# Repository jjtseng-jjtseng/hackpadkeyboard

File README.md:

# My HackPad Keyboard

A keyboard that can type an absurdly large amount of characters in a short space.
By combining the 16 keys with the knob, each turn of the knob makes each key type a different thing. This way, you can go from your normal A B C's to weird hieroglyphics.

# Features/Things used:

- 3d printed case (bottom section with a usb c hole wita top cover with a knob and key hole(s))
- 99.5 x99.5 mm pcb with a 4x4 matrix of buttons on it (+ knob)
- 16 LED's for each of buttons (cool lighting effects)

# CAD
Used fusion 360
Pretty easy. Bottom case with usb c hole + top case with key, knob, and LED holes.

# PCB

PCB pics attached below.
Kicad used

Schematic

PCB
CAD render:

# Firmware:
Python with a main.py used.

#How the final product should look:

Main.py

# BOM

Everything that is needed to make this:

- 1x custom pcb
- 1x Rotary encoder
- 1x Seeed XIAO RP2040
- 16x SK6812MINI-E RGB LEDs
- 16x DSA keycaps
- 16x 1N4148 Diodes

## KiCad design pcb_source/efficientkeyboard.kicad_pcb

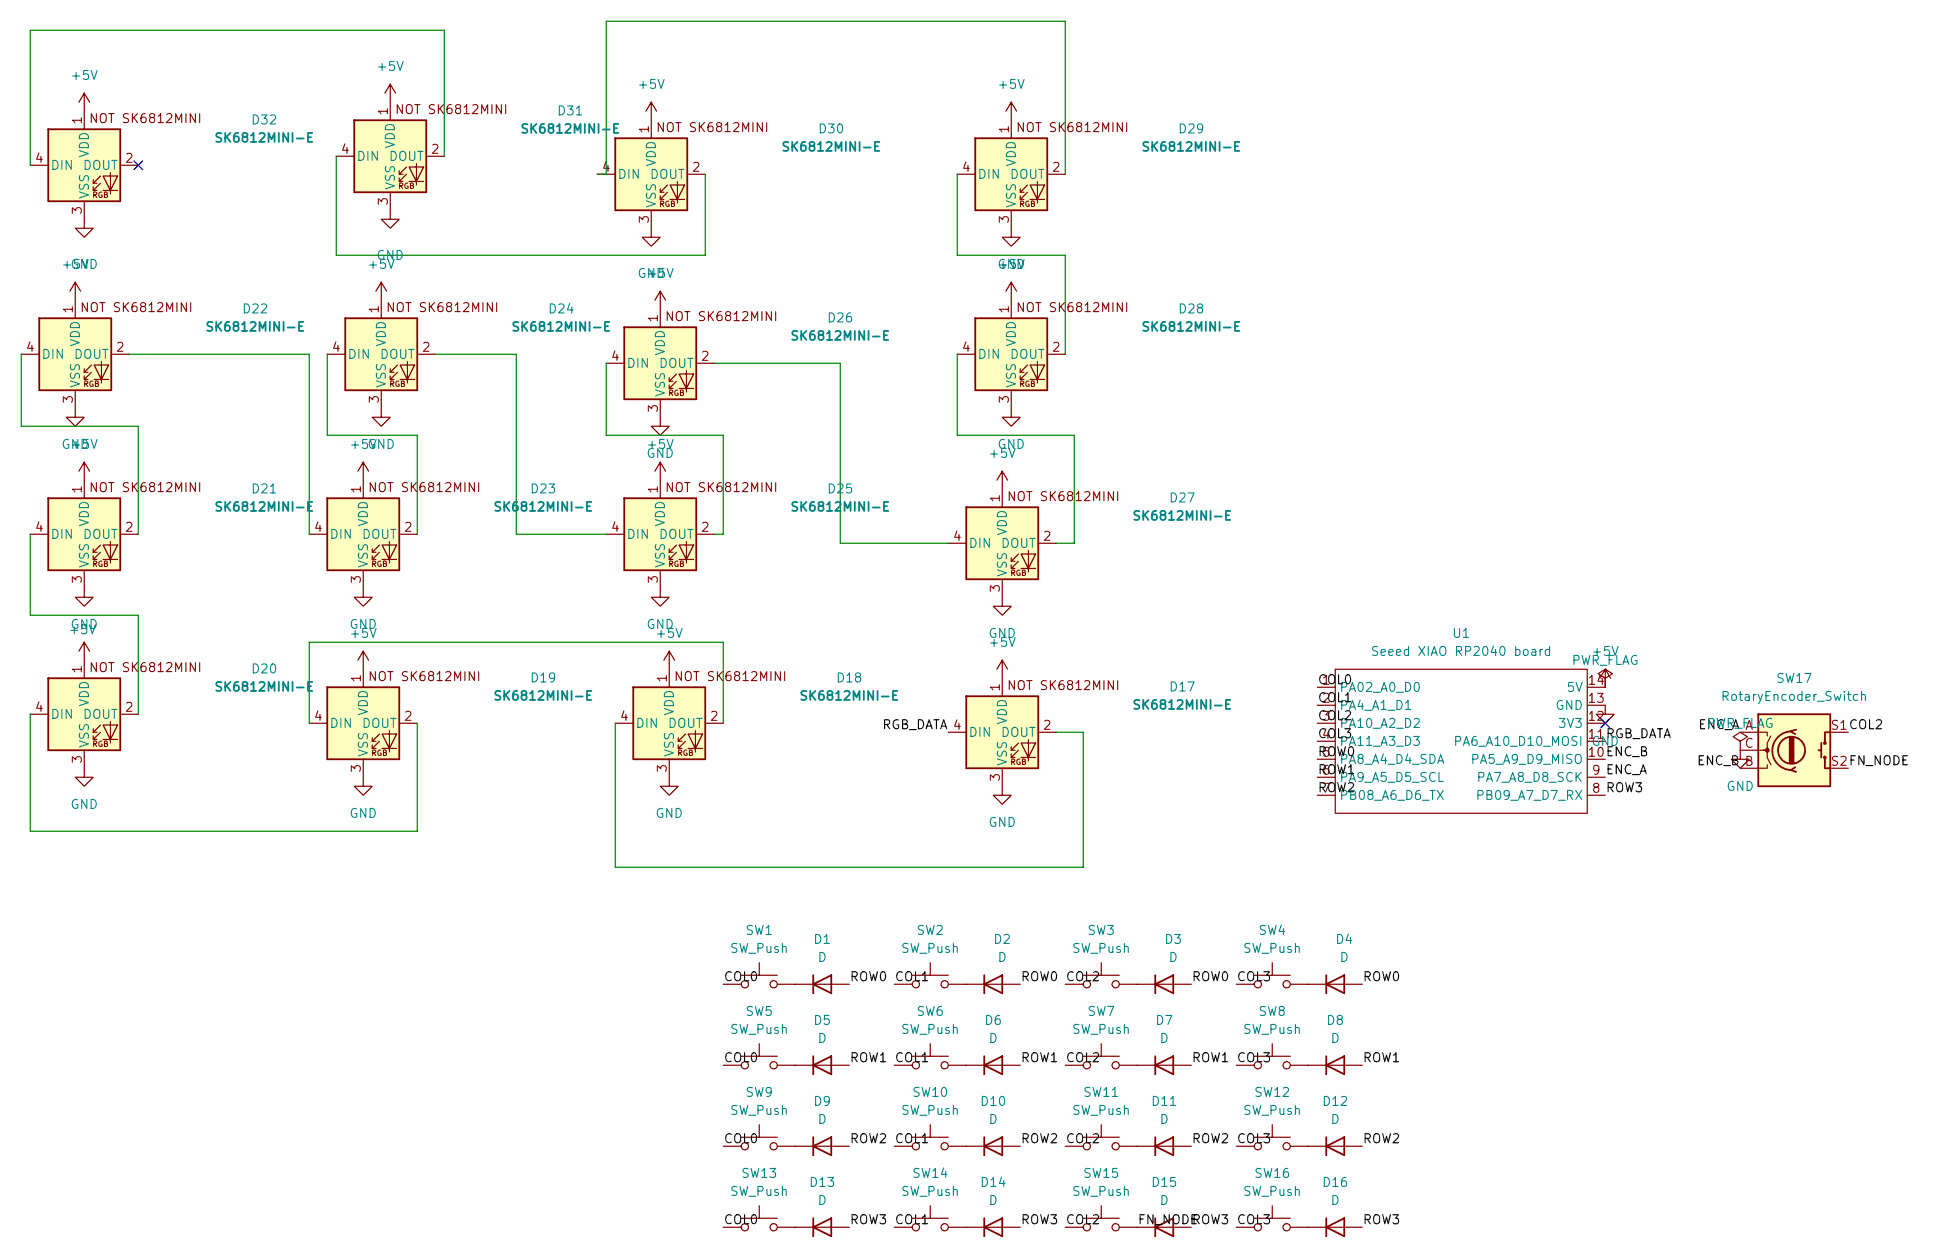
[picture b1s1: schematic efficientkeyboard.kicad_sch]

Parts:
D1, D2, D3, D4, D5, D6, D7, D8, D9, D10, D11, D12, D13, D14, D15, D16: D; D_DO-35_SOD27_P7.62mm_Horizontal
D17, D18, D19, D20, D21, D22, D23, D24, D25, D26, D27, D28, D29, D30, D31, D32: SK6812MINI-E; SK6812MINI-E_keyboard
SW1, SW2, SW3, SW4, SW5, SW6, SW7, SW8, SW9, SW10, SW11, SW12, SW13, SW14, SW15: SW_Push; SW_Cherry_MX_1.00u_PCB
SW16: SW_Push; SW_Cherry_MX_keyboard
SW17: RotaryEncoder_Switch; RotaryEncoder_Alps_EC11E-Switch_Vertical_H20mm
U1: Seeed XIAO RP2040 board; XIAO-Generic-Hybrid-keyboard

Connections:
+5V: D17.1 (VDD), D18.1 (VDD), D19.1 (VDD), D20.1 (VDD), D21.1 (VDD), D22.1 (VDD), D23.1 (VDD), D24.1 (VDD), D25.1 (VDD), D26.1 (VDD), D27.1 (VDD), D28.1 (VDD), D29.1 (VDD), D30.1 (VDD), D31.1 (VDD), D32.1 (VDD), U1.14 (5V)
/COL0: SW1.1, SW5.1, SW9.1, SW13.1, U1.1 (PA02_A0_D0)
/COL1: SW2.1, SW6.1, SW10.1, SW14.1, U1.2 (PA4_A1_D1)
/COL2: SW3.1, SW7.1, SW11.1, SW15.1, SW17.S1, U1.3 (PA10_A2_D2)
/COL3: SW4.1, SW8.1, SW12.1, SW16.1, U1.4 (PA11_A3_D3)
/ENC_A: SW17.A, U1.9 (PA7_A8_D8_SCK)
/ENC_B: SW17.B, U1.10 (PA5_A9_D9_MISO)
/FN_NODE: D15.1 (K), SW15.2, SW17.S2
/RGB_DATA: D17.4 (DIN), U1.11 (PA6_A10_D10_MOSI)
/ROW0: D1.2 (A), D2.2 (A), D3.2 (A), D4.2 (A), U1.5 (PA8_A4_D4_SDA)
/ROW1: D5.2 (A), D6.2 (A), D7.2 (A), D8.2 (A), U1.6 (PA9_A5_D5_SCL)
/ROW2: D9.2 (A), D10.2 (A), D11.2 (A), D12.2 (A), U1.7 (PB08_A6_D6_TX)
/ROW3: D13.2 (A), D14.2 (A), D15.2 (A), D16.2 (A), U1.8 (PB09_A7_D7_RX)
GND: D17.3 (VSS), D18.3 (VSS), D19.3 (VSS), D20.3 (VSS), D21.3 (VSS), D22.3 (VSS), D23.3 (VSS), D24.3 (VSS), D25.3 (VSS), D26.3 (VSS), D27.3 (VSS), D28.3 (VSS), D29.3 (VSS), D30.3 (VSS), D31.3 (VSS), D32.3 (VSS), SW17.C, U1.13 (GND)
unnamed: D1.1 (K), SW1.2
unnamed: D2.1 (K), SW2.2
unnamed: D3.1 (K), SW3.2
unnamed: D4.1 (K), SW4.2
unnamed: D5.1 (K), SW5.2
unnamed: D6.1 (K), SW6.2
unnamed: D7.1 (K), SW7.2
unnamed: D8.1 (K), SW8.2
unnamed: D9.1 (K), SW9.2
unnamed: D10.1 (K), SW10.2
unnamed: D11.1 (K), SW11.2
unnamed: D12.1 (K), SW12.2
unnamed: D13.1 (K), SW13.2
unnamed: D14.1 (K), SW14.2
unnamed: D16.1 (K), SW16.2
unnamed: D17.2 (DOUT), D18.4 (DIN)
unnamed: D18.2 (DOUT), D19.4 (DIN)
unnamed: D19.2 (DOUT), D20.4 (DIN)
unnamed: D20.2 (DOUT), D21.4 (DIN)
unnamed: D21.2 (DOUT), D22.4 (DIN)
unnamed: D22.2 (DOUT), D23.4 (DIN)
unnamed: D23.2 (DOUT), D24.4 (DIN)
unnamed: D24.2 (DOUT), D25.4 (DIN)
unnamed: D25.2 (DOUT), D26.4 (DIN)
unnamed: D26.2 (DOUT), D27.4 (DIN)
unnamed: D27.2 (DOUT), D28.4 (DIN)
unnamed: D28.2 (DOUT), D29.4 (DIN)
unnamed: D29.2 (DOUT), D30.4 (DIN)
unnamed: D30.2 (DOUT), D31.4 (DIN)
unnamed: D31.2 (DOUT), D32.4 (DIN)

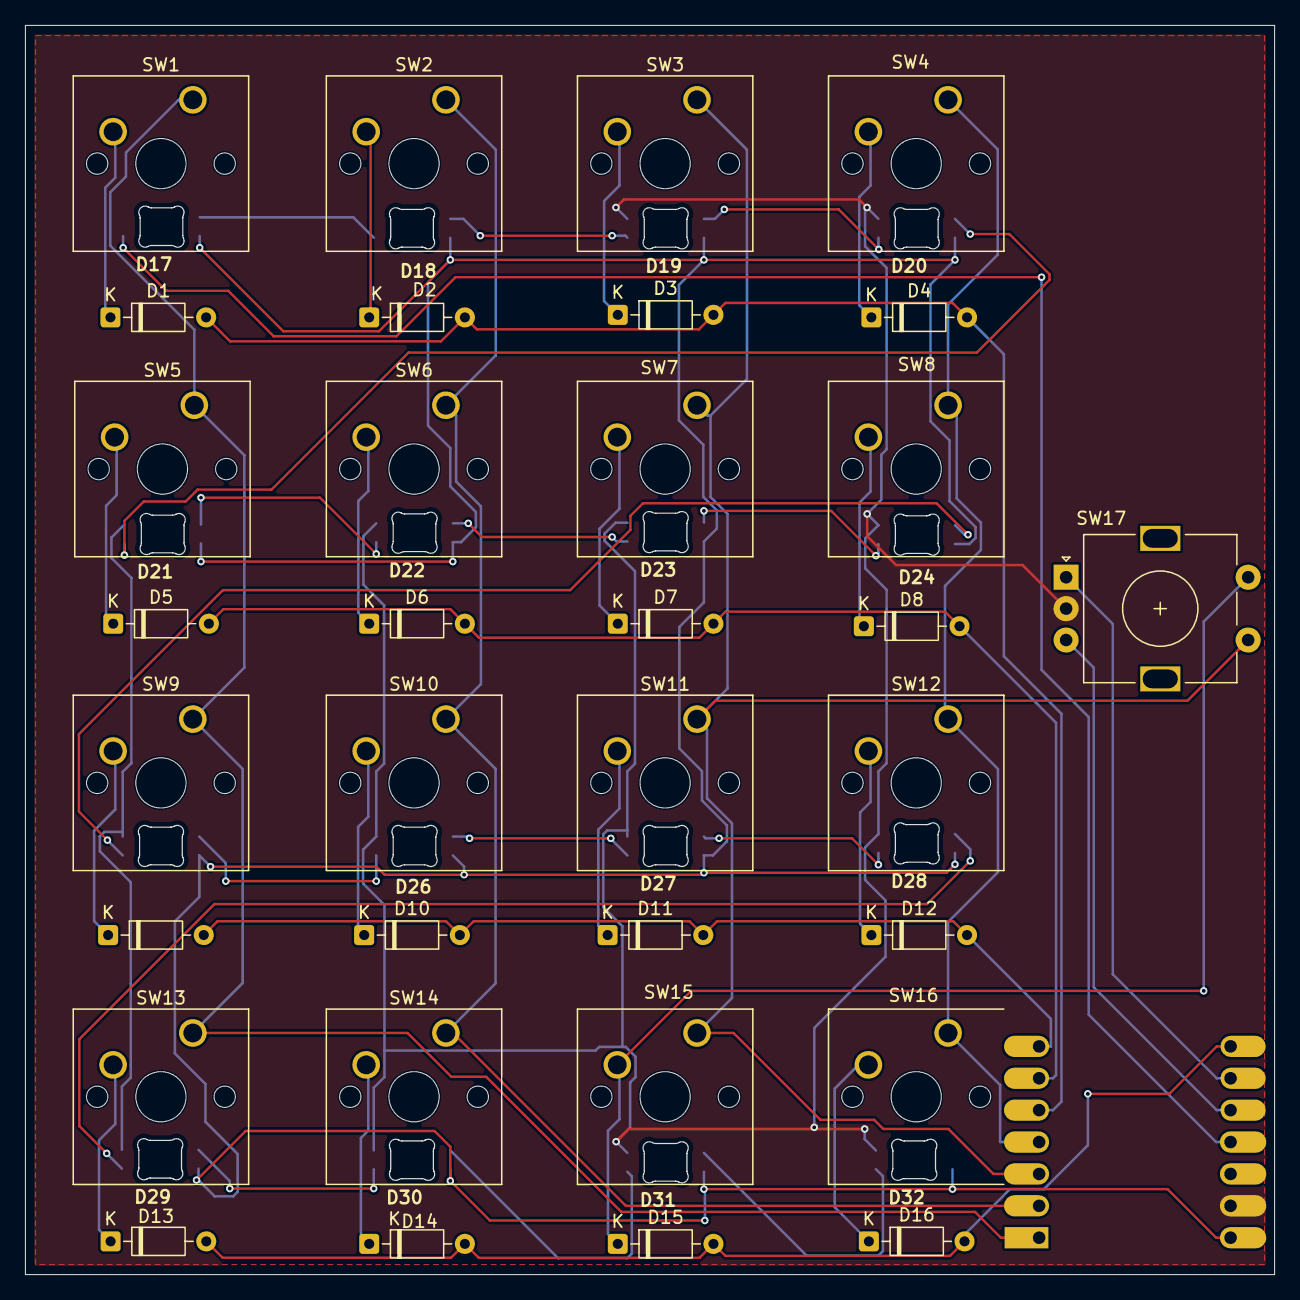
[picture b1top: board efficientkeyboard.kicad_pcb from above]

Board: 2 copper layers, 99.5 x 99.5 mm, 50 parts (1 on the bottom side), 44 nets.
